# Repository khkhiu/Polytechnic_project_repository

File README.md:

# Polytechnic project repository
This repository contains a summary of all projects I did when studying for a Diploma in Electrical and Electronic Engineering(DEEE) in Singapore Polytechnic (SP).

***
<cite><a href="https://github.com/khkhiu/Polytechnic_project_repository/tree/main/Computer-Aided_Design_Keychain_and_Desk_Organiser">Project: Computer-Aided Design Keychain and Desk Organiser</a></cite>
***
A keychain and desk organiser designed using Computer-Aided Drafting(CAD) software. Completed in Year 1 Semester 1. 
<br>
<br>

***
<cite><a href="https://github.com/khkhiu/Polytechnic_project_repository/tree/main/Digital_Electronics_Stop_Watch">Project: Digital Electronics Stop Watch</a></cite>
***
A stop watch built using simple electronic components. Compeleted in Year 1 Semester 2.
<br>
<br>

***
<cite><a href="https://github.com/khkhiu/Polytechnic_project_repository/tree/main/Arduino_Solar-Wind_Hybrid_Power_Generator">Project: Arduino Solar-Wind Hybrid Power Generator</a></cite>
***
A project built for SP's 2nd introduction to engineering module. Completed in Year 1 Semester 2.
<br>
<br>

***
<cite><a href="https://github.com/khkhiu/Polytechnic_project_repository/tree/main/Data_analytics_with_Knime">Project: Data Analytics with Knime</a></cite>
***
The project done for SP's 'Statistics and Analytics for Engineers(SAE)' module. Completed in Year 2 Semester 1.
<br>
<br>

***
<cite><a href="https://github.com/khkhiu/Polytechnic_project_repository/tree/main/PIC18_Microcontroller_Solar-Hydro_Hybrid_Power_Generator">Project: PIC18 Solar-Hydro Power Generator</a></cite>
***
An improved hybrid power generation project. Completed in Year 2 Semester 1.
<br>
<br>

***
<cite><a href="https://github.com/khkhiu/Polytechnic_project_repository/tree/main/FPGA_Vending_Machine">Project: FPGA vending machine</a></cite>
***
Simulation of a vending machine using a Basys3 Field Programmable Gate Array(FPGA). Completed in Year 2 Semester 1.
<br>
<br>

***
<cite><a href="https://github.com/khkhiu/Polytechnic_project_repository/tree/main/Centroid_Counter_using_OpenCV_in_Python">Project: Python Centroid Counter</a></cite>
***
A centroid counter programmed in python. Completed in Year 2 Semester 1.
<br>
<br>

***
<cite><a href="https://github.com/khkhiu/Polytechnic_project_repository/tree/main/Programmable_Logic_Controller_Vending_Machine">Project: PLC vending machine</a></cite>
***
Simulation of a vending machine using a Siemens Programmable Logic Controller(PLC). Completed in Year 2 Semester 2.
<br>
<br>

***
<cite><a href="https://github.com/khkhiu/Polytechnic_project_repository/tree/main/EEE_Notes">EEE Notes</a></cite>
***
Most notes, tutorials and past-year papers for Singapore Polytechnic's Diploma in Electrical Electronic Engineering (DEEE) for Academic Years 2020 to 2023.

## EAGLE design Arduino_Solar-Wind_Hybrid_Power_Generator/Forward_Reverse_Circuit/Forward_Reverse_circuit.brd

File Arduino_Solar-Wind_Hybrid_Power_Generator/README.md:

# Singapore Polytechnic - Engineering Design and Solution Project

***

<strong>Introductions</strong>

***
'Introduction to Engineering' aims equips students with engineering fundamentals set in the context of CDIO (conceive, design, implement and operate) in real-world systems with basic electronic projects. It aims to nurture students toward self-directed learners by giving them a challenging environment to plan, manage, review and extend their learning outcomes using growth mind-set and meta-cognitive learning systems in achieving their electronic projects. Besides, students will be exposed to a range of generic process skills such as troubleshooting skills, creative and critical thinking, teamwork and communication.

'Engineering & Engineering Design Solutions' is a continuation of 'Introduction to Engineering'. This module aims to nurture students toward self-directed learners by giving them a more challenging environment to plan, manage, review and extend their learning outcomes using growth mind and meta-cognitive learning systems in achieving their electronic projects.

***

<strong>Task - Engineering Design Solutions</strong>

***
The team was tasked to come up with a project that would address one of the UN Sustainable Development Goals. 

<em>Image of UN SDG</em>

Students were provided with the following items:

<em>Custom Arduino made in SP</em>

<em>Counter unit</em>

<em>Target sensors</em>

<em>Voltage regulator with relay</em>

<em>Pulse generator</em>

<em>Forward-Reverse circuit, students had to mill this themselves</em>

***

<strong>The team</strong>

***
The team consisted of the following people, all of whom were from Singapore Polytechnic(SP) taking Diploma in Electrical and Electronic Engineering(DEEE)(As of 31 March 2021)

1. Khiu Kim Hong
2. Ngo Bing Han
3. Low Jun Jie

***

<strong>Solution - Engineering Design Solutions</strong>

***
The team decided to address Goal 7: 'Ensure access to affordable, reliable, sustainable and modern energy for all'. An issue with solar power is that it is unable to generated power at night. Therefore, by adding wind power to solar power, we can ensure that energy is generated in the day and at night.

***

<strong>Video Demonstration</strong>

***

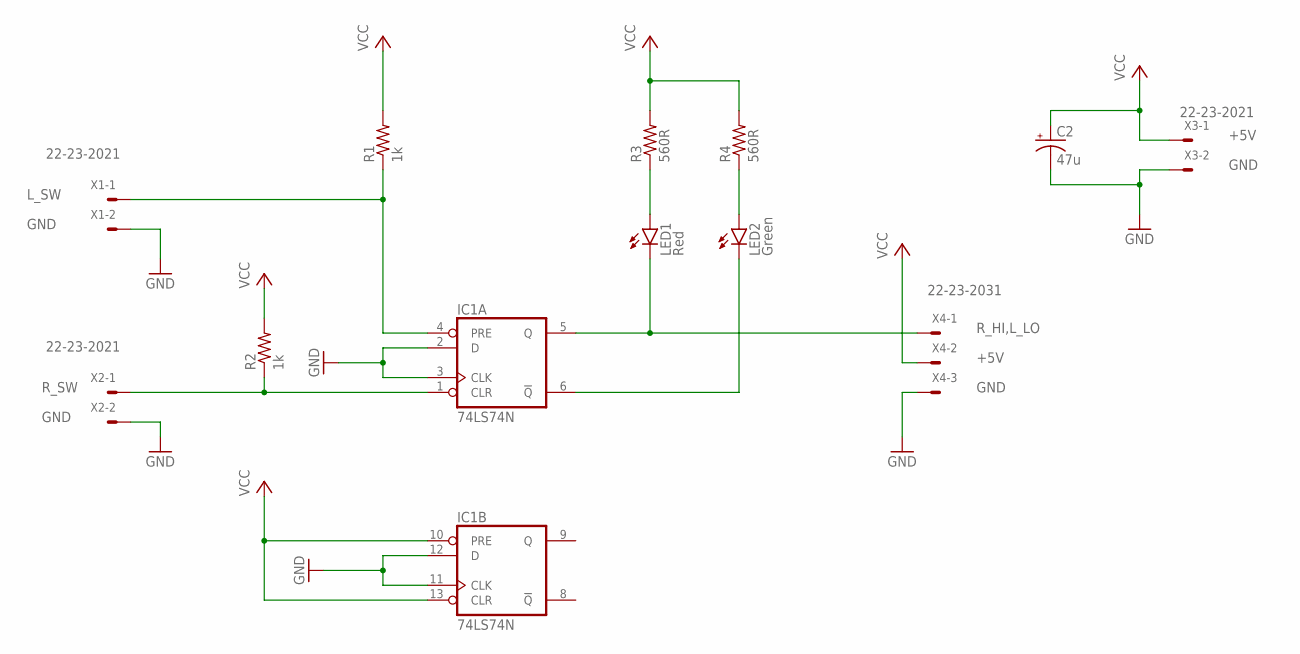
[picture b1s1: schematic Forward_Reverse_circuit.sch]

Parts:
C2: 47u; E5-6
IC1: 74LS74N; DIL14
LED1: Red; LED5MM
LED2: Green; LED5MM
R1, R2: 1k; 0207/12
R3, R4: 560R; 0207/12
X1, X2, X3: 22-23-2021
X4: 22-23-2031

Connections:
+5V: C2.+, IC1.10 (PRE), IC1.13 (CLR), IC1.14 (VCC), R1.2, R2.2, R3.2, R4.2, X3.1, X4.2
GND: C2.-, IC1.2 (D), IC1.3 (CLK), IC1.7 (GND), IC1.11 (CLK), IC1.12 (D), X1.2, X2.2, X3.2, X4.3
L_SW: IC1.4 (PRE), R1.1, X1.1
unnamed: IC1.6 (!Q), LED2.K (C)
unnamed: LED2.A, R4.1
unnamed: LED1.A, R3.1
R_HI,L_LO: IC1.5 (Q), LED1.K (C), X4.1
R_SW: IC1.1 (CLR), R2.1, X2.1

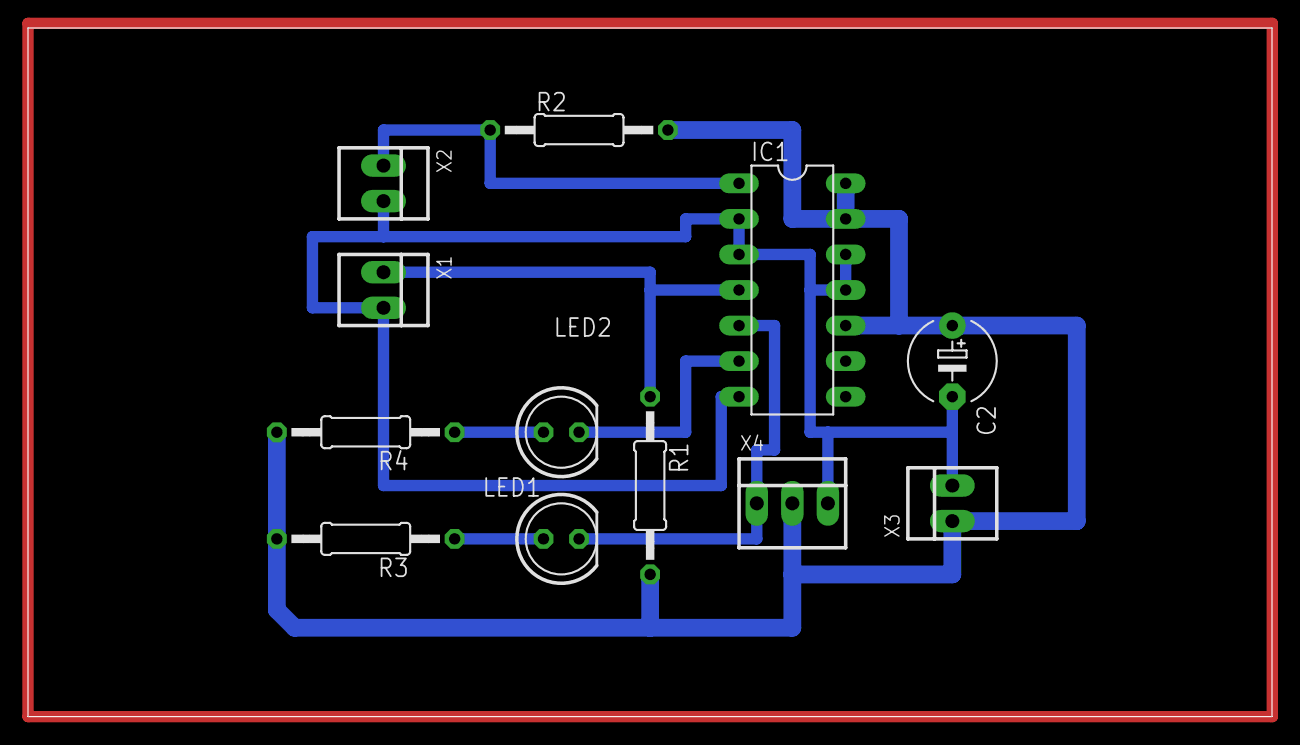
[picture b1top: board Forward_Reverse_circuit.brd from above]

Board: 2 copper layers, 88.9 x 49.2 mm, 12 parts (0 on the bottom side), 8 nets.

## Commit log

2023-08-20 Uploaded project folders
2023-11-04 Uploaded EEE Notes
2023-11-04 Uploaded files for EEE notes
